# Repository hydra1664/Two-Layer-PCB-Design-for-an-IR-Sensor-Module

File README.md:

# Two-Layer PCB for IR Sensor Module

This project is a custom-designed two-layer PCB for an infrared (IR) proximity sensor module, created using KiCad 9.0. The aim was to build a compact and reliable board that could be used for object detection, proximity sensing, or reflective surface detection.  

The module is built around three main parts:
- An IR LED to emit infrared light
- A photodiode to detect the reflected light
- An op-amp comparator to process the signal and output a clean digital logic level  

The design was done with manufacturing in mind, keeping the board simple, efficient, and noise-resistant.

## Schematic Design

The schematic includes:
- IR LED for transmitting modulated IR light  
- Photodiode for sensing reflected light  
- Op-amp comparator for generating a digital HIGH/LOW output  
- Resistor network for biasing and setting comparator thresholds  

## PCB Layout

Component placement:
- IR LED and photodiode are placed at the edge of the board for proper optical alignment with the environment  
- The op-amp is placed centrally to allow balanced trace routing  
- Custom footprints were used in some cases to simplify routing and save space  

Routing strategy:
- Sensitive signals (especially the photodiode output) are kept short and direct to reduce noise  
- A ground plane was added to the bottom layer for shielding and noise reduction  
- Power and output signals are routed on the top layer with standard trace widths  
- Vias are minimized to maintain signal integrity  
- Components are clearly labeled on the silkscreen  

## Files Included

The repository includes the following files:
- 2-Layer-Proximity-PCB.kicad_pcb – the PCB layout  
- 2-Layer-Proximity-PCB.kicad_sch – the schematic file  
- Gerbers/ – a folder containing the full Gerber set, exported in JLCPCB format and ready for fabrication  

## Verification

The design was checked using KiCad’s DRC (Design Rule Check) and ERC (Electrical Rule Check) tools to ensure it meets both electrical and manufacturing requirements.  

## Conclusion

This PCB design provides a simple but effective IR sensor module that is well-suited for small-scale proximity detection applications. Working on this project gave me more hands-on experience in PCB design, especially with handling analog signals and optimizing layouts for sensor performance.

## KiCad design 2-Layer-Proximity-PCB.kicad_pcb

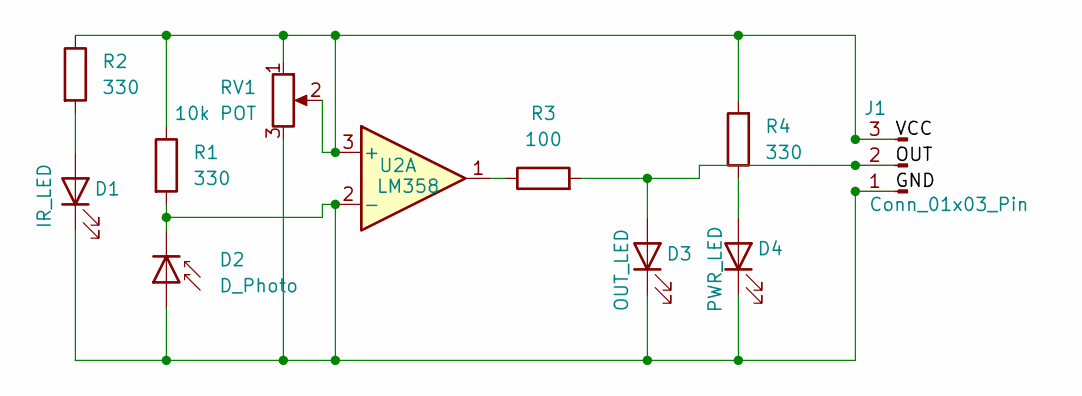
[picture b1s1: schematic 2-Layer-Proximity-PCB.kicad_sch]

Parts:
D1: IR_LED; LED_D5.0mm_Horizontal_O3.81mm_Z3.0mm
D2: D_Photo; LED_D5.0mm_Horizontal_O3.81mm_Z3.0mm
D3: OUT_LED; LED_0805_2012Metric_Pad1.15x1.40mm_HandSolder
D4: PWR_LED; LED_0805_2012Metric_Pad1.15x1.40mm_HandSolder
J1: Conn_01x03_Pin; PinHeader_1x03_P2.54mm_Horizontal
R1, R2, R4: 330; R_0805_2012Metric
R3: 100; R_0805_2012Metric
RV1: 10k POT; Potentiometer_ACP_CA9-V10_Vertical_Hole
U2: LM358; SOIC-8_3.9x4.9mm_P1.27mm

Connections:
/GND: D1.1 (K), D2.1 (K), D2.2 (A), D3.1 (K), D4.1 (K), J1.1, R1.2, RV1.3, U2.2 (-)
/OUT: D3.2 (A), J1.2, R3.2
/VCC: J1.3, R1.1, R2.1, R4.2, RV1.1, RV1.2, U2.3 (+)
unnamed: D1.2 (A), R2.2
unnamed: D4.2 (A), R4.1
unnamed: R3.1, U2.1

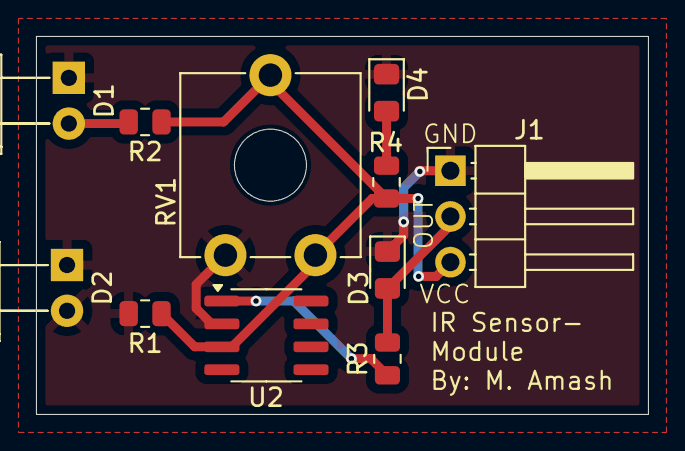
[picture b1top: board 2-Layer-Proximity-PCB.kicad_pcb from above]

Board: 2 copper layers, 34.0 x 21.0 mm, 11 parts (0 on the bottom side), 6 nets.

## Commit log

2025-08-20 Uploaded Gerbers, Schematics and PCB Design files
